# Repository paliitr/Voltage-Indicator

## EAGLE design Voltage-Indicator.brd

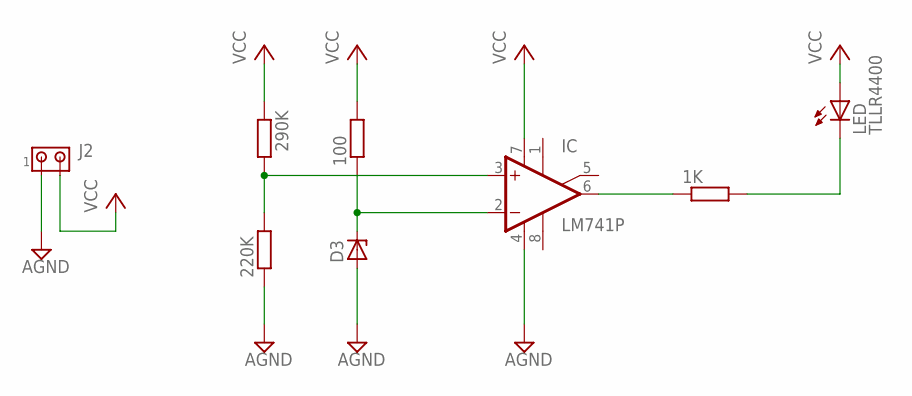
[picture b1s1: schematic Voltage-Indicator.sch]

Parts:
1K, 100, 220K, 290K: R-EU_0204/7; 0204/7
D3: ZENER-DIODEDO35Z10; DO35Z10
IC: LM741P; DIL08
J2: MTA02-100; 10X02MTA
LED: TLLR4400; LED3MM

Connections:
GND: 220K.1, D3.A, IC.4 (V-), J2.1
IC: 1K.1, IC.6 (OUT)
unnamed: 1K.2, LED.K (C)
unnamed: 100.1, D3.C, IC.2 (-IN)
unnamed: 220K.2, 290K.2, IC.3 (+IN)
VCC: 100.2, 290K.1, IC.7 (V+), J2.2, LED.A

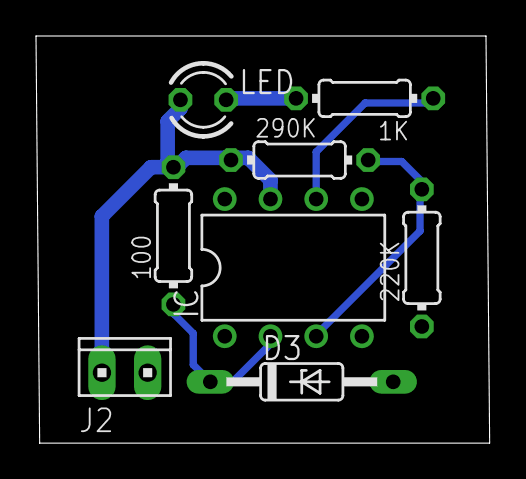
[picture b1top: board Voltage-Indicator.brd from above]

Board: 2 copper layers, 25.2 x 22.6 mm, 8 parts (0 on the bottom side), 6 nets.

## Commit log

2015-09-29 :boom::camel: Added .gitattributes & .gitignore files
2015-09-29 Intial Commit
